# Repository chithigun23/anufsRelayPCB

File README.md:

# Engine Shutoff Safety System – 6-Relay PCB

## Overview

This project involves the design and development of a custom PCB that controls six relays as part of an engine shutoff safety system for a Formula Student race car. The system is a critical component of the vehicle's overall electrical safety and is designed to ensure that the engine can be safely and reliably disabled in an emergency.

## Features

- **Six Relay Outputs**: Current rated components and appropriate PCB traces.
- **Fail-Safe Design**: Uses normally open relays
- **Compact Layout**: Designed for minimal space in a tight race car.

## PCB Specifications

| Feature             | Details                               |
|---------------------|----------------------------------------|
| Number of Relays    | 6                                     |
| Relay Type          | SPDT        |
| Control Voltage     | 12V         |
| Power Supply        | 12V DC                |
| Protection Features | Flyback diode  |
| Board Size          | TBD            |
| Mounting            | Rubber grommits to limit shock and vibration|

## System Block Diagram

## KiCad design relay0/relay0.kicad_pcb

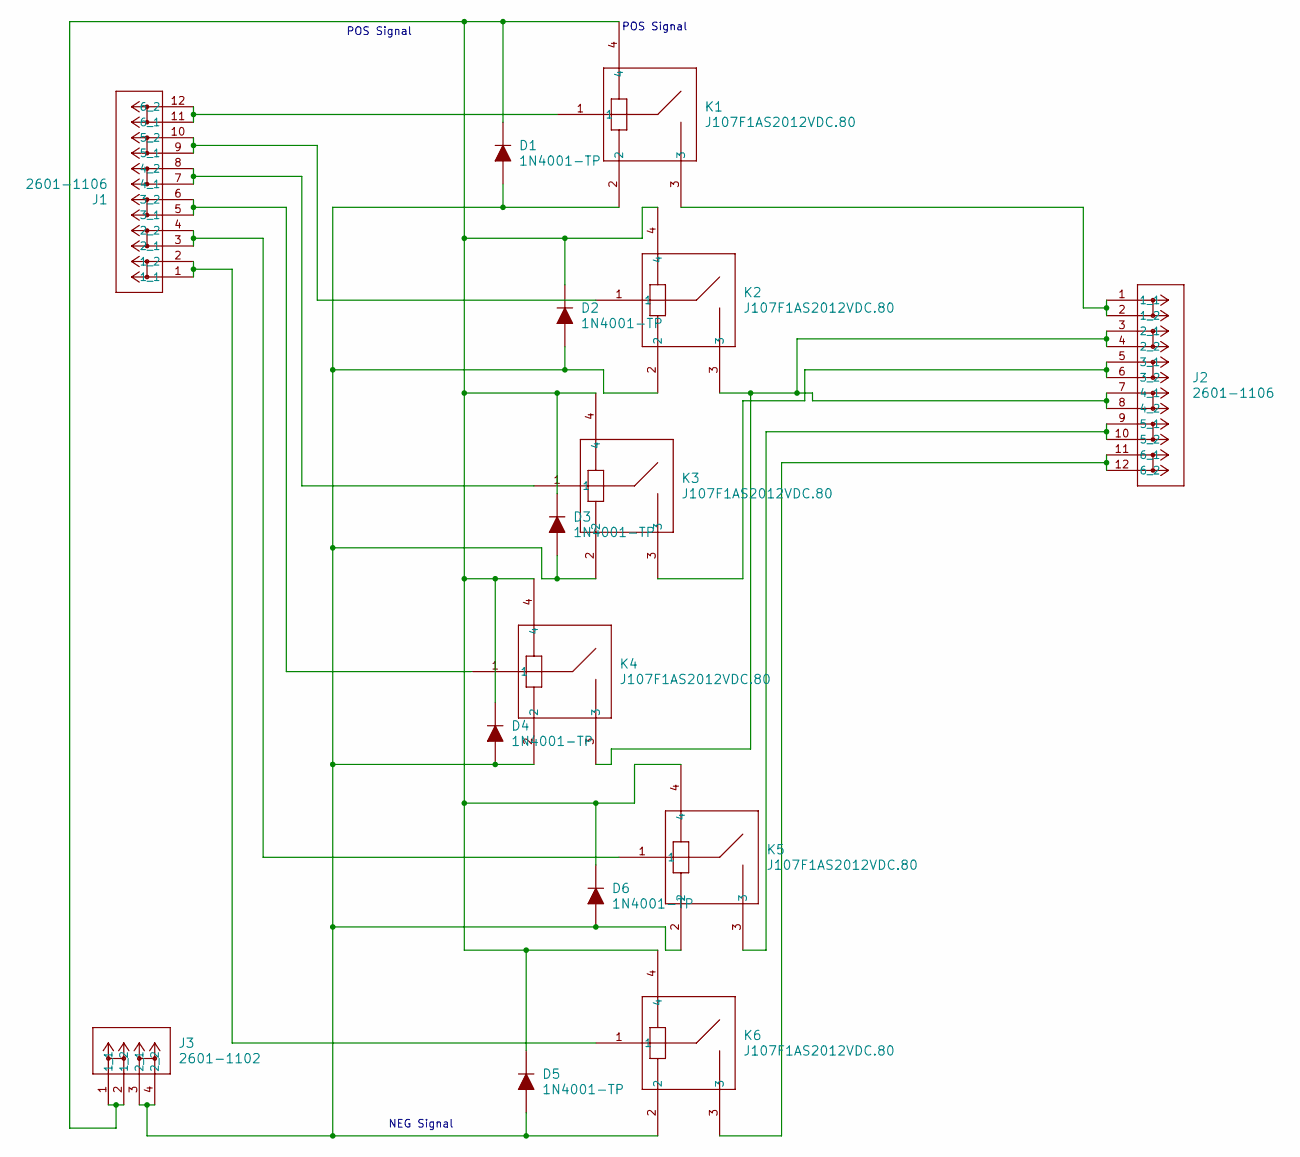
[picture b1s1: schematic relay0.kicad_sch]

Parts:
D1, D2, D3, D4, D5, D6: 1N4001-TP; DO-41; MPN 1N4001-TP; Digi-Key_PN 1N4001-TPMSCT-ND
J1, J2: 2601-1106; CONN6_2601-1106_WAG
J3: 2601-1102; CONN2_2601-1102_WAG
K1, K2, K3, K4, K5, K6: J107F1AS2012VDC.80; RELAY_J107F1A_CRS

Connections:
unnamed: J1.1 (1_1), J1.2 (1_2), K6.1
unnamed: J1.3 (2_1), J1.4 (2_2), K5.1
unnamed: J1.5 (3_1), J1.6 (3_2), K4.1
unnamed: J1.7 (4_1), J1.8 (4_2), K3.1
unnamed: J1.9 (5_1), J1.10 (5_2), K2.1
unnamed: J1.11 (6_1), J1.12 (6_2), K1.1
unnamed: J2.1 (1_1), J2.2 (1_2), K1.3
unnamed: J2.3 (2_1), J2.4 (2_2), J2.7 (4_1), J2.8 (4_2), K2.3, K4.3
unnamed: J2.5 (3_1), J2.6 (3_2), K3.3
unnamed: J2.9 (5_1), J2.10 (5_2), K5.3
unnamed: J2.11 (6_1), J2.12 (6_2), K6.3
unnamed: D1.K, D2.K, D3.K, D4.K, D5.K, D6.K, J3.1 (1_1), J3.2 (1_2), K1.4, K2.4, K3.4, K4.4, K5.4, K6.4
unnamed: D1.A, D2.A, D3.A, D4.A, D5.A, D6.A, J3.3 (2_1), J3.4 (2_2), K1.2, K2.2, K3.2, K4.2, K5.2, K6.2

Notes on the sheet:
POS Signal
NEG Signal

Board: 2 copper layers, 15 parts (0 on the bottom side), 13 nets, no tracks yet.

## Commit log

2025-06-17 Readme updates
2025-06-19 PCB Design updates
